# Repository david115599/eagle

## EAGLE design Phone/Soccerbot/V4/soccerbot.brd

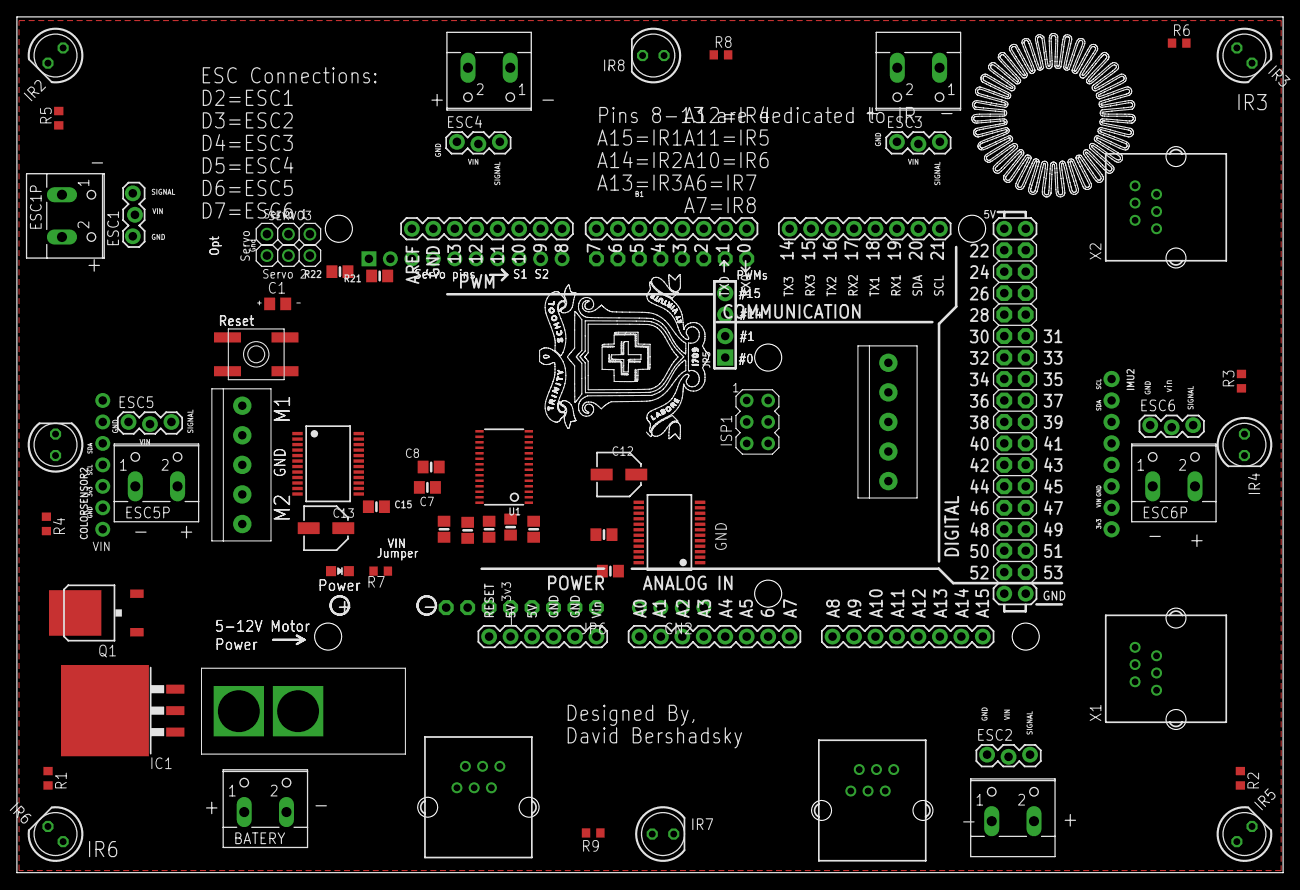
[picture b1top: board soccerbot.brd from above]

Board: 2 copper layers, 149.8 x 101.3 mm, 70 parts (0 on the bottom side), 67 nets, no tracks yet.

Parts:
B1: ARDUINO_MEGA_R3FULL; ARDUINO_MEGA
BATERY: W237-102
C1: C0805
C7, C8, C11: 0.1uF; 0805-NO
C12: 47uF/16v; PANASONIC_C
C13: 47uF+/16v; PANASONIC_C
C15, C16: 10uF; 0805-NO
CN2: 1X4-CLEANBIG; 1X04-CLEANBIG
COLORSENSOR2: 1X07_ROUND_70
D0-1: 1X08-CLEANBIG
ESC1, ESC2, ESC3, ESC4, ESC5, ESC6: 1X03_LOCK
ESC1P, ESC2P, ESC3P, ESC4P, ESC5P, ESC6P: W237-102
IC1: LM340S-05; TO263-3
IC2, IC4: SSOP24
IMU2: 1X08_ROUND_76
IR1, IR2, IR3, IR4, IR5, IR6, IR7, IR8: LED5MM
ISP1: AVRISP-6; AVRISP
J3, J4: 1X5; 1X05-3.5MM
JP5: 1X04_ROUND_76
JP6: 1X08-CLEANBIG
JP7: 1X10_ROUND70
LED2: Green; CHIPLED_0805_NOOUTLINE
Q1: AOD417; D-PAK_TO252AA
R1, R2, R3, R5, R6, R8, R9: 49.9k; R0603
R4: R0603
R7: 150ohm; R0603
R15, R16, R17, R19, R20: 0805-NO
R21, R22: 10K; 0805-NO
SERVO3, SERVO4: 1X03
SW2: SPST_TACT-EVQQ2; EVQ-Q2
U1: PCA9685; TSSOP28
U$2: TOGGLESWITCH
X1, X2, X3, X4: NXT-SOCKET

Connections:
3.3V: B1.3.3V, JP6.5, X1.4, X2.4, X3.4, X4.4
5.5V: B1.5V@0, B1.5V@1, B1.5V@2, C7.1, C8.1, C11.1, C15.1, C16.1, COLORSENSOR2.1, ESC1.2, ESC2.2, ESC3.2, ESC4.2, ESC5.2, ESC6.2, IC2.19, IC2.20, IC4.19, IC4.20, IMU2.7, IR1.K, IR2.K, IR3.K, IR4.K, IR5.K, IR6.K, IR7.K, IR8.K, ISP1.2, JP6.4, LED2.A, R21.2, R22.2, U1.24, U1.28
A0: R15.2, U1.1
A0A: B1.A0, CN2.4
A1: R16.2, U1.2
A1A: B1.A1, CN2.3
A2: R17.2, U1.3
A2A: B1.A2, CN2.2
A3: R19.2, U1.4
A3A: B1.A3, CN2.1
A4: R20.2, U1.5
A6: B1.A6, IR7.A, R9.1
A7: B1.A7, IR8.A, R8.1
A10: B1.A10, IR6.A, R1.1
A11: B1.A11, IR5.A, R2.1
A12: B1.A12, IR4.A, R3.1
A13: B1.A13, IR3.A, R6.1
A14: B1.A14, IR2.A, R5.1
A15: B1.A15, IR1.A, R4.1
AREF: B1.AREF, JP7.3
BAT+: B1.VIN, C12.+, C13.+, ESC1P.2, ESC2P.2, ESC3P.2, ESC4P.2, ESC5P.2, ESC6P.2, IC1.3, IC2.13, IC2.14, IC2.24, IC4.13, IC4.14, IC4.24, JP6.1, Q1.4, X1.1, X2.1, X3.1, X4.1
D0: B1.0, D0-1.1
D1: B1.1, D0-1.2
D2: B1.2, D0-1.3, ESC1.3
D3: B1.3, D0-1.4, ESC2.3
D4: B1.4, D0-1.5, ESC3.3
D5: B1.5, D0-1.6, ESC4.3
D6: B1.6, D0-1.7, ESC5.3
D7: B1.7, D0-1.8, ESC6.3
D8: B1.8, JP7.10
D9: B1.9, JP7.9, SERVO4.3
D10: B1.10, JP7.8, SERVO3.3
D11: B1.11, JP7.7
D12: B1.12, JP7.6
D13: B1.13, JP7.5
GND: B1.GND@0, B1.GND@1, B1.GND@2, B1.GND@3, B1.GND@4, BATERY.2, C1.2, C7.2, C8.2, C11.2, C12.-, C13.-, C15.2, C16.2, COLORSENSOR2.2, ESC1.1, ESC1P.1, ESC2.1, ESC2P.1, ESC3.1, ESC3P.1, ESC4.1, ESC4P.1, ESC5.1, ESC5P.1, ESC6.1, ESC6P.1, IC1.1, IC2.3, IC2.4, IC2.9, IC2.10, IC2.18, IC4.3, IC4.4, IC4.9, IC4.10, IC4.18, IMU2.6, ISP1.6, J3.3, J4.3, JP6.2, JP6.3, JP7.4, Q1.1, R1.2, R2.2, R3.2, R4.2, R5.2, R6.2, R7.1, R8.2, R9.2, R15.1, R16.1, R17.1, R19.1, R20.1, SERVO3.1, SERVO4.1, SW2.A, SW2.A', U1.14, U1.23, U1.25, X1.2, X1.3, X2.2, X2.3, X3.2, X3.3, X4.2, X4.3
M1A1: IC2.1, IC2.2, J3.5
M1B1: IC2.5, IC2.6, J3.4
M2A1: IC2.11, IC2.12, J3.1
M2B1: IC2.7, IC2.8, J3.2
M3A1: IC4.1, IC4.2, J4.1
M3B1: IC4.5, IC4.6, J4.2
M4A1: IC4.11, IC4.12, J4.5
M4B1: IC4.7, IC4.8, J4.4
unnamed: LED2.C, R7.2
unnamed: BATERY.1, U$2.IN
unnamed: Q1.3, U$2.OUT
PWM0: JP5.1, U1.6
PWM1: JP5.2, U1.7
PWM2: IC4.23, U1.8
PWM3: IC4.22, U1.9
PWM4: IC4.21, U1.10
PWM5: IC4.17, U1.11
PWM6: IC4.16, U1.12
PWM7: IC4.15, U1.13
PWM8: IC2.23, U1.15
PWM9: IC2.22, U1.16
PWM10: IC2.21, U1.17
PWM11: IC2.17, U1.18
PWM12: IC2.16, U1.19
PWM13: IC2.15, U1.20
PWM14: JP5.3, U1.21
PWM15: JP5.4, U1.22
RESET: B1.RESET, JP6.6, SW2.B, SW2.B'
SCL: B1.21, B1.A5, COLORSENSOR2.4, IMU2.1, JP7.1, R22.1, U1.26, X1.5, X2.5, X3.5, X4.5
SDA: B1.20, B1.A4, COLORSENSOR2.5, IMU2.2, JP7.2, R21.1, U1.27, X1.6, X2.6, X3.6, X4.6
SERVO5V: C1.1, IC1.TAB, SERVO3.2, SERVO4.2

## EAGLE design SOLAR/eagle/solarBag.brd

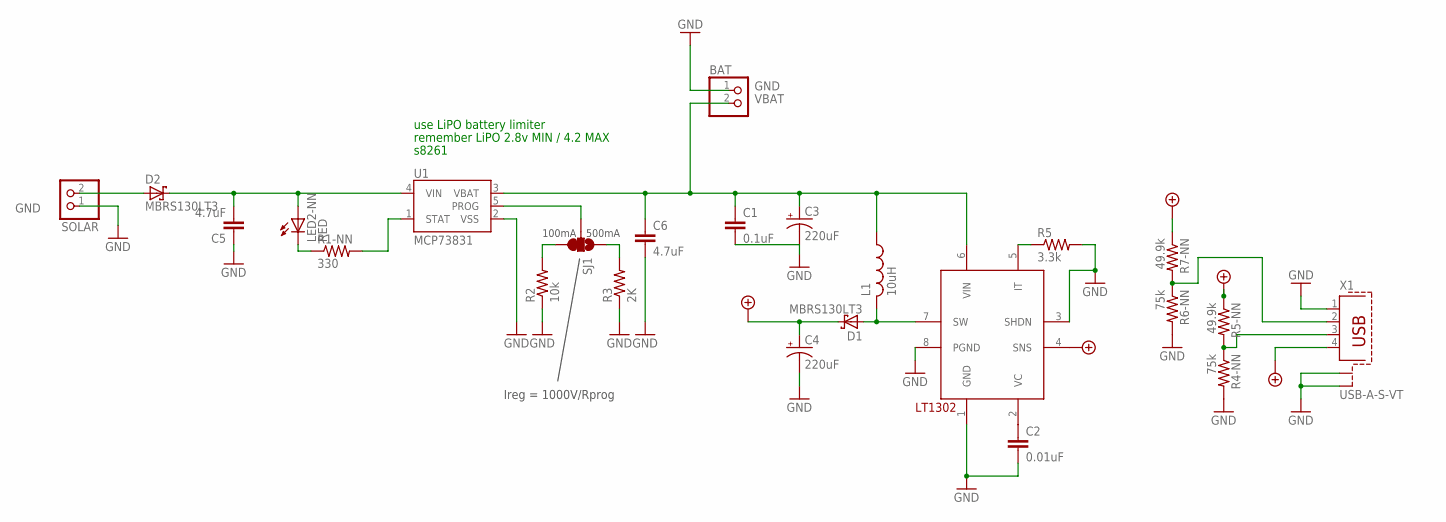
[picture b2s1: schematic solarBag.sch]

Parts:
BAT: PINHD-1X2; 1X02
C1: 0.1uF; C1206
C2: 0.01uF; C1206
C3, C4: 220uF; PANASONIC_F@1
C5, C6: 4.7uF; C1206
D1, D2: MBRS130LT3; SMB
L1: 10uH; SDR0403
LED2-NN: RED; LED-1206
R1-NN: 330; R1206
R2: 10k; R1206
R3: 2K; R1206
R4-NN, R6-NN: 75k; R0805
R5: 3.3k; R0805
R5-NN, R7-NN: 49.9k; R1206
SJ1: SOLDERJUMPER_2WAYS; SJ_3
SOLAR: PINHD-1X2; 1X02
U1: MCP73831; SOT23-5
U2: LT1302; SOIC8
X1: USB-A-S-VT

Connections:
+5V: C4.+, D1.C, R5-NN.1, R7-NN.1, U2.4 (SNS), X1.4
D+: R6-NN.1, R7-NN.2, X1.2
D-: R4-NN.1, R5-NN.2, X1.3
GND: BAT.1, C1.2, C2.2, C3.-, C4.-, C5.1, C6.2, R2.1, R3.1, R4-NN.2, R5.2, R6-NN.2, SOLAR.1, U1.2 (VSS), U2.1 (GND), U2.3 (SHDN), U2.8 (PGND), X1.1, X1.S1, X1.S2
unnamed: D1.A, L1.P$2 (2), U2.7 (SW)
unnamed: R1-NN.2, U1.1 (STAT)
unnamed: R2.2, SJ1.3
unnamed: R5.1, U2.5 (IT)
unnamed: LED2-NN.C, R1-NN.1
unnamed: R3.2, SJ1.1
unnamed: C2.1, U2.2 (VC)
unnamed: C5.2, D2.C, LED2-NN.A, U1.4 (VIN)
unnamed: D2.A, SOLAR.2
PROG: SJ1.2, U1.5 (PROG)
VBAT: BAT.2, C1.1, C3.+, C6.1, L1.P$1 (1), U1.3 (VBAT), U2.6 (VIN)

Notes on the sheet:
100mA
500mA
Ireg = 1000V/Rprog
remember LiPO 2.8v MIN / 4.2 MAX
s8261
use LiPO battery limiter

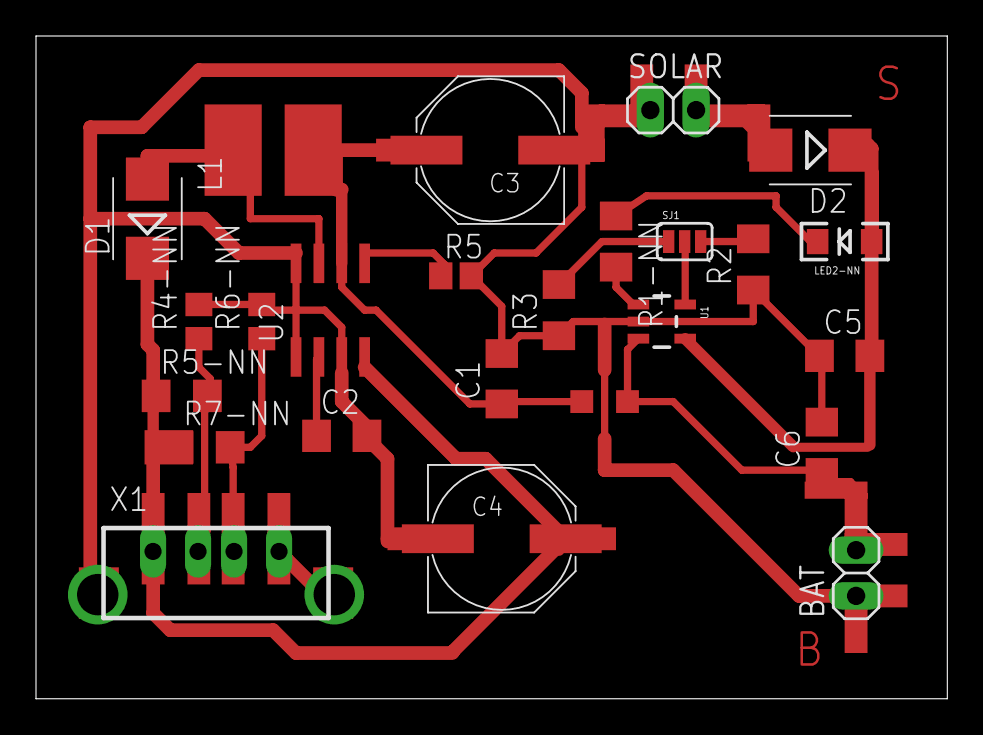
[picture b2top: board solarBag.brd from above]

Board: 2 copper layers, 50.6 x 36.8 mm, 24 parts (0 on the bottom side), 15 nets.

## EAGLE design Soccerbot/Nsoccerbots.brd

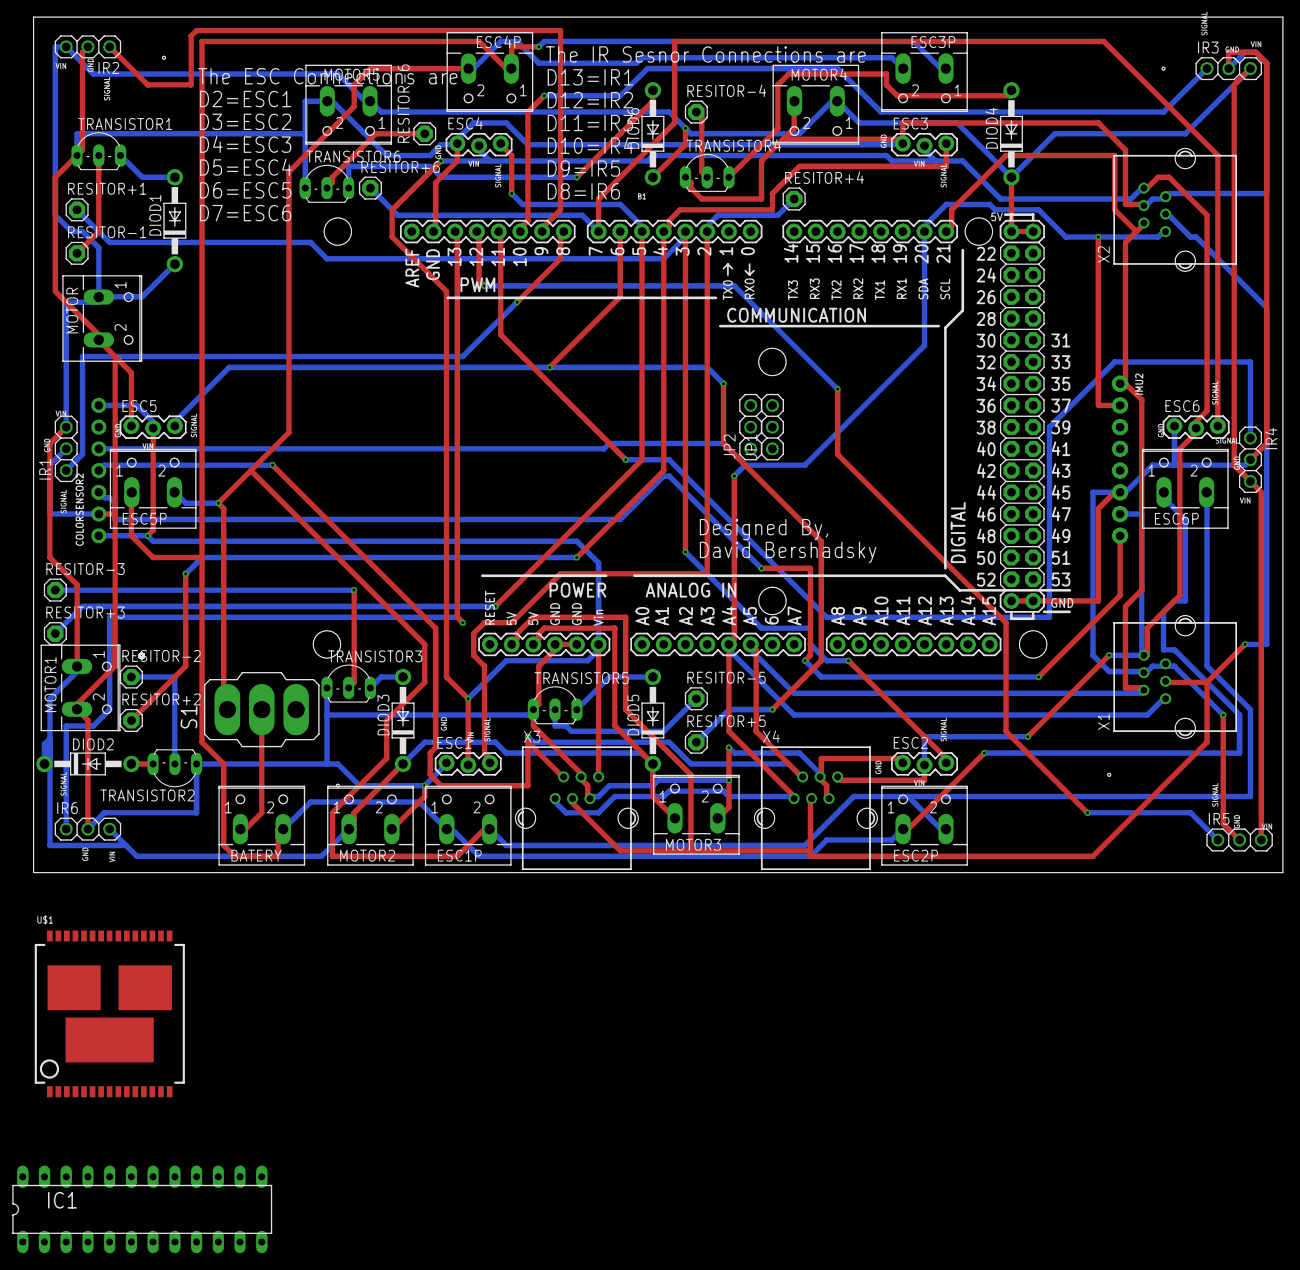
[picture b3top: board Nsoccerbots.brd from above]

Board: 2 copper layers, 146.0 x 100.0 mm, 61 parts (0 on the bottom side), 34 nets.

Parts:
B1: ARDUINO_MEGA_R3FULL; ARDUINO_MEGA
BATERY: W237-102
COLORSENSOR2: 1X07_ROUND_70
DIOD1, DIOD2, DIOD3, DIOD4, DIOD5, DIOD6: 1N4004; DO41-10
ESC1, ESC2, ESC3, ESC4, ESC5, ESC6: 1X03_LOCK
ESC1P, ESC2P, ESC3P, ESC4P, ESC5P, ESC6P: W237-102
IC1: 33035P; DIL24S
IMU2: 1X08_ROUND_76
IR1, IR2, IR3, IR4, IR5, IR6: 1X03
JP1, JP2: 1X03
MOTOR, MOTOR1, MOTOR2, MOTOR3, MOTOR4, MOTOR5: W237-102
RESITOR+1, RESITOR+2, RESITOR+3, RESITOR+4, RESITOR+5, RESITOR+6: 1X01
RESITOR-1, RESITOR-2, RESITOR-3, RESITOR-4, RESITOR-5, RESITOR-6: 1X01
S1: 320-916
TRANSISTOR1, TRANSISTOR2, TRANSISTOR3, TRANSISTOR4, TRANSISTOR5, TRANSISTOR6: 2N2907; TO92-EBC-OVAL
U$1: VNH2SP30
X1, X2, X3, X4: NXT-SOCKET

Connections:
3.3V: B1.3.3V, X1.4, X2.4, X3.4, X4.4
5.5V: B1.5V@0, B1.5V@1, B1.5V@2, DIOD1.C, DIOD2.C, DIOD3.C, DIOD4.C, DIOD5.C, DIOD6.C, IR1.3, IR2.3, IR3.3, IR4.3, IR5.3, IR6.3, MOTOR.1, MOTOR1.1, MOTOR2.1, MOTOR3.1, MOTOR4.1, MOTOR5.1
+3V3: COLORSENSOR2.3, IMU2.8
BAT+: ESC1P.2, ESC2P.2, ESC3P.2, ESC4P.2, ESC5P.2, ESC6P.2, S1.1
BAT-: BATERY.2, ESC1P.1, ESC2P.1, ESC3P.1, ESC4P.1, ESC5P.1, ESC6P.1
D2: B1.2, ESC1.3, RESITOR+4.1
D3: B1.3, ESC2.3, RESITOR+1.1
D4: B1.4, ESC3.3, RESITOR+2.1
D5: B1.5, ESC4.3, RESITOR+3.1
D6: B1.6, ESC5.3, RESITOR+5.1
D7: B1.7, ESC6.3, RESITOR+6.1
D8: B1.8, IR1.1
D9: B1.9, IR2.1
D10: B1.10, IR3.1
D11: B1.11, IR4.1
D12: B1.12, IR5.1
D13: B1.13, IR6.1
GND: B1.GND@0, B1.GND@1, B1.GND@2, B1.GND@3, B1.GND@4, COLORSENSOR2.2, ESC1.1, ESC2.1, ESC3.1, ESC4.1, ESC5.1, ESC6.1, IC1.16, IMU2.6, IR1.2, IR2.2, IR3.2, IR4.2, IR5.2, IR6.2, MOTOR.2, MOTOR1.2, MOTOR2.2, MOTOR3.2, MOTOR4.2, MOTOR5.2, TRANSISTOR1.E, TRANSISTOR2.E, TRANSISTOR3.E, TRANSISTOR4.E, TRANSISTOR5.E, TRANSISTOR6.E, X1.2, X1.3, X2.2, X2.3, X3.2, X3.3, X4.2, X4.3
unnamed: RESITOR-1.1, TRANSISTOR1.B
unnamed: DIOD1.A, TRANSISTOR1.C
unnamed: RESITOR-4.1, TRANSISTOR4.B
unnamed: BATERY.1, S1.2
unnamed: RESITOR-2.1, TRANSISTOR2.B
unnamed: DIOD2.A, TRANSISTOR2.C
unnamed: RESITOR-3.1, TRANSISTOR3.B
unnamed: DIOD3.A, TRANSISTOR3.C
unnamed: RESITOR-5.1, TRANSISTOR5.B
unnamed: DIOD5.A, TRANSISTOR5.C
unnamed: DIOD4.A, TRANSISTOR4.C
unnamed: RESITOR-6.1, TRANSISTOR6.B
unnamed: DIOD6.A, TRANSISTOR6.C
SCL: B1.21, B1.A5, COLORSENSOR2.4, IMU2.1, X1.5, X2.5, X3.5, X4.5
SDA: B1.20, B1.A4, COLORSENSOR2.5, IMU2.2, X1.6, X2.6, X3.6, X4.6
VIN: B1.VIN, COLORSENSOR2.1, COLORSENSOR2.7, ESC1.2, ESC2.2, ESC3.2, ESC4.2, ESC5.2, ESC6.2, IMU2.7, X1.1, X2.1, X3.1, X4.1

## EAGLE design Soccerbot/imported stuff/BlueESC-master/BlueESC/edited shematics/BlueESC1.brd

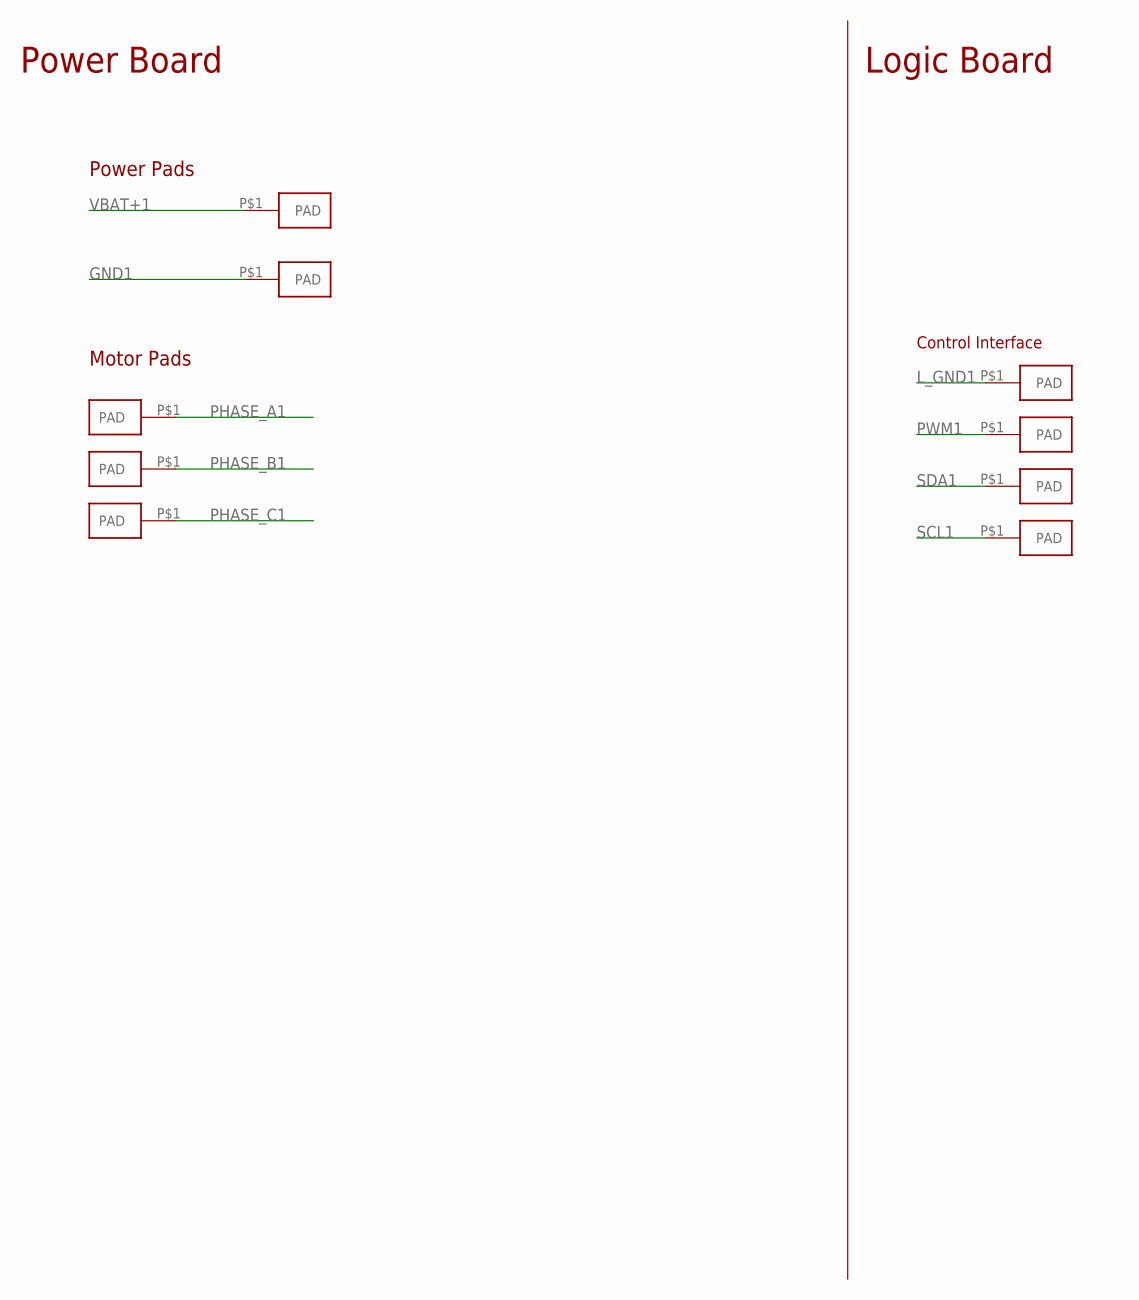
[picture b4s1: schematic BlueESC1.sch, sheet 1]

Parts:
U$1, U$2: PADPTH-MED; PAD-PTH-MED-1
U$5, U$6, U$7: PAD18AWG; PAD-PTH-18AWG-1
U$11, U$12, U$13, U$14: PAD1.5X3MM; PAD-1.5X3MM

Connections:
GND1: U$2.P$1; also elsewhere on the board
L_GND1: U$11.P$1; also elsewhere on the board
PHASE_A1: U$5.P$1; also elsewhere on the board
PHASE_B1: U$6.P$1; also elsewhere on the board
PHASE_C1: U$7.P$1; also elsewhere on the board
PWM1: U$14.P$1; also elsewhere on the board
SCL1: U$13.P$1; also elsewhere on the board
SDA1: U$12.P$1; also elsewhere on the board
VBAT+1: U$1.P$1; also elsewhere on the board

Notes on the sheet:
Power Pads
Motor Pads
Control Interface
Power Board
Logic Board

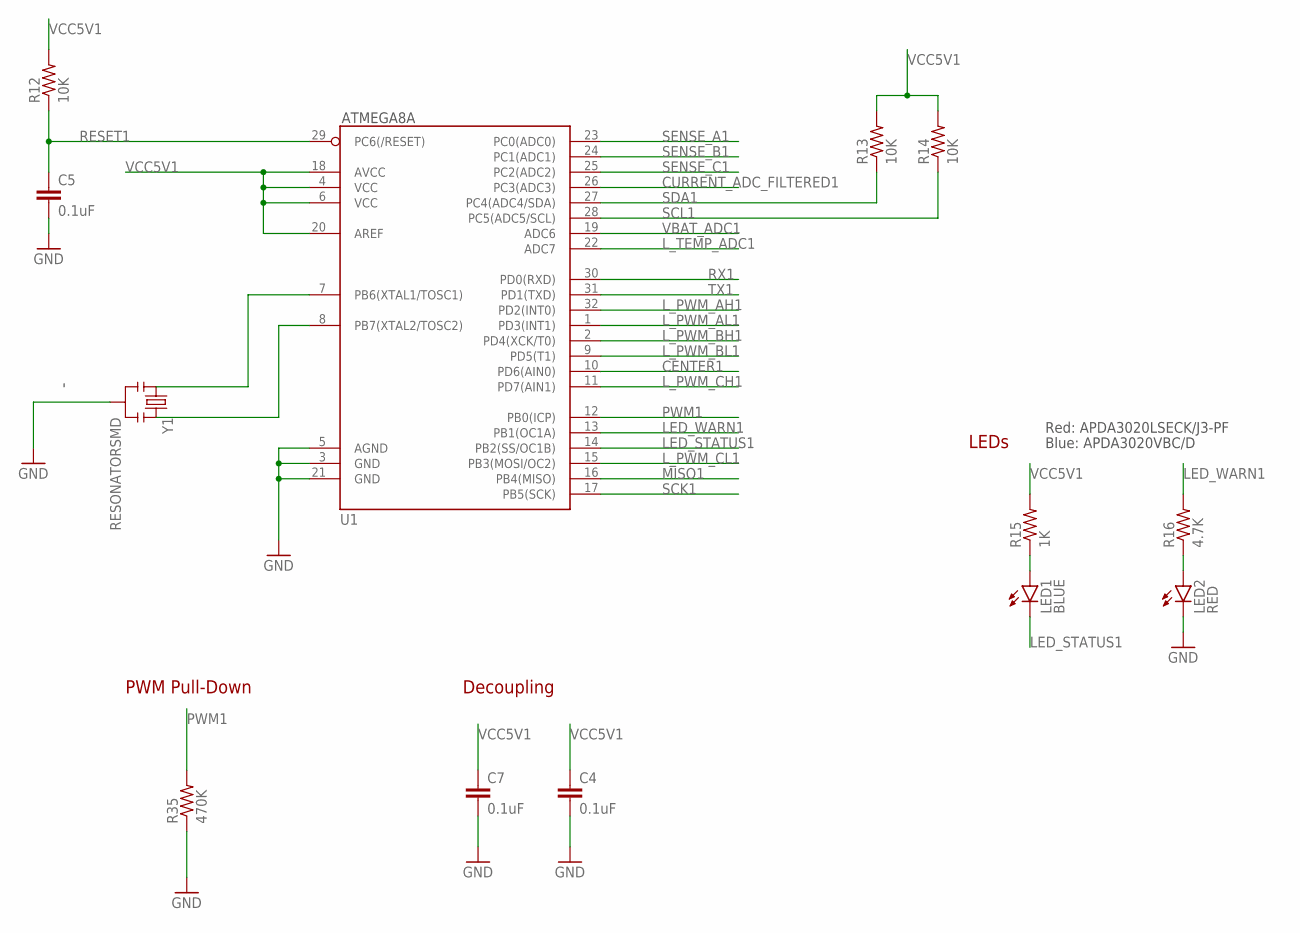
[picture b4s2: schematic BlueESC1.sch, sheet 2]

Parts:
C4, C5, C7: 0.1uF; 0603-CAP
LED1: BLUE; SMT-LED-3X2-RA
LED2: RED; SMT-LED-3X2-RA
R12, R13, R14: 10K; 0603-RES
R15: 1K; 0603-RES
R16: 4.7K; 0603-RES
R35: 470K; 0603-RES
U1: ATMEGA168; TQFP32-08
Y1: RESONATORSMD; RESONATOR-SMD

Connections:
CENTER1: U1.10 (PD6(AIN0)); also elsewhere on the board
CURRENT_ADC_FILTERED1: U1.26 (PC3(ADC3)); also elsewhere on the board
LED_STATUS1: LED1.2 (C), U1.14 (PB2(SS/OC1B))
LED_WARN1: R16.2, U1.13 (PB1(OC1A))
L_GND1: C4.2, C5.2, C7.2, LED2.2 (C), R35.1, U1.3 (GND), U1.5 (AGND), U1.21 (GND), Y1.2; also elsewhere on the board
L_PWM_AH1: U1.32 (PD2(INT0))
L_PWM_AL1: U1.1 (PD3(INT1))
L_PWM_BH1: U1.2 (PD4(XCK/T0))
L_PWM_BL1: U1.9 (PD5(T1))
L_PWM_CH1: U1.11 (PD7(AIN1))
L_PWM_CL1: U1.15 (PB3(MOSI/OC2))
L_TEMP_ADC1: U1.22 (ADC7)
MISO1: U1.16 (PB4(MISO))
unnamed: LED2.1 (A), R16.1
unnamed: U1.7 (PB6(XTAL1/TOSC1)), Y1.1
unnamed: U1.8 (PB7(XTAL2/TOSC2)), Y1.3
unnamed: LED1.1 (A), R15.1
PWM1: R35.2, U1.12 (PB0(ICP)); also elsewhere on the board
RESET1: C5.1, R12.1, U1.29 (PC6(/RESET))
RX1: U1.30 (PD0(RXD))
SCK1: U1.17 (PB5(SCK))
SCL1: R14.1, U1.28 (PC5(ADC5/SCL)); also elsewhere on the board
SDA1: R13.1, U1.27 (PC4(ADC4/SDA)); also elsewhere on the board
SENSE_A1: U1.23 (PC0(ADC0)); also elsewhere on the board
SENSE_B1: U1.24 (PC1(ADC1)); also elsewhere on the board
SENSE_C1: U1.25 (PC2(ADC2)); also elsewhere on the board
TX1: U1.31 (PD1(TXD))
VBAT_ADC1: U1.19 (ADC6); also elsewhere on the board
VCC5V1: C4.1, C7.1, R12.2, R13.2, R14.2, R15.2, U1.4 (VCC), U1.6 (VCC), U1.18 (AVCC), U1.20 (AREF); also elsewhere on the board

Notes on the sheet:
ATMEGA8A
Decoupling
LEDs
Red: APDA3020LSECK/J3-PF
Blue: APDA3020VBC/D
PWM Pull-Down

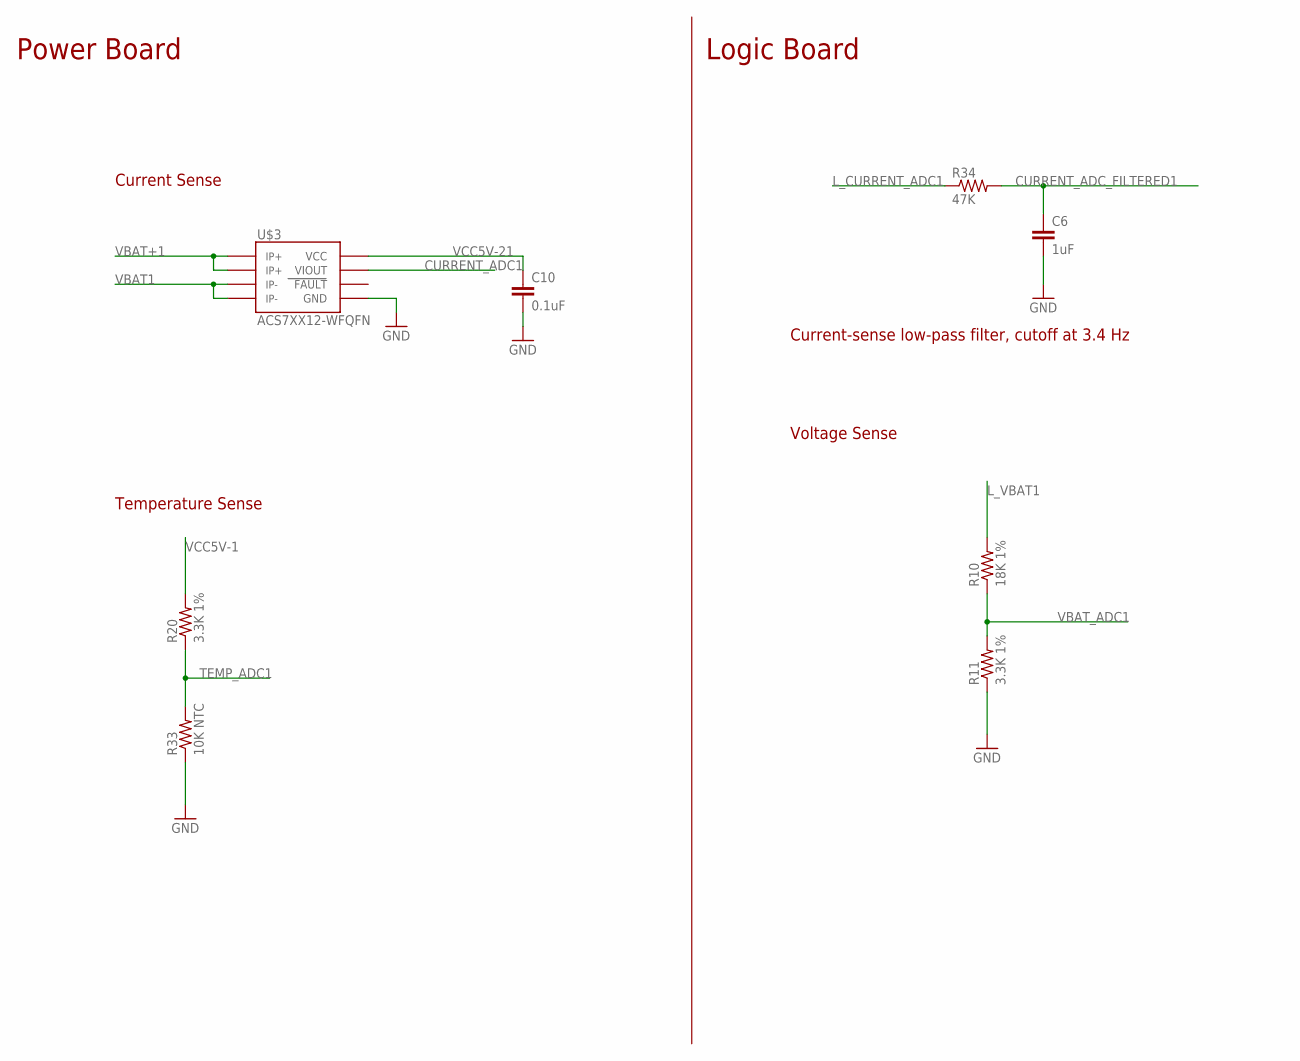
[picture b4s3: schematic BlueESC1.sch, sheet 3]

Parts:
C6: 1uF; 0603-CAP
C10: 0.1uF; 0603-CAP
R10: 18K 1%; 0603-RES
R11, R20: 3.3K 1%; 0603-RES
R33: 10K NTC; 0603-RES
R34: 47K; 0603-RES
U$3: ACS7XX12-WFQFN; 12-WFQFN

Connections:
CURRENT_ADC1: U$3.VIOUT
CURRENT_ADC_FILTERED1: C6.1, R34.2; also elsewhere on the board
GND1: C10.2, R33.1, U$3.GND; also elsewhere on the board
L_CURRENT_ADC1: R34.1
L_GND1: C6.2, R11.1; also elsewhere on the board
L_VBAT1: R10.2; also elsewhere on the board
TEMP_ADC1: R20.1, R33.2
VBAT1: U$3.IP-1, U$3.IP-2; also elsewhere on the board
VBAT+1: U$3.IP+1, U$3.IP+2; also elsewhere on the board
VBAT_ADC1: R10.1, R11.2; also elsewhere on the board
VCC5V-1: R20.2
VCC5V-21: C10.1, U$3.VCC

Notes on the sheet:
Power Board
Logic Board
Current-sense low-pass filter, cutoff at 3.4 Hz
Voltage Sense
Current Sense
Temperature Sense

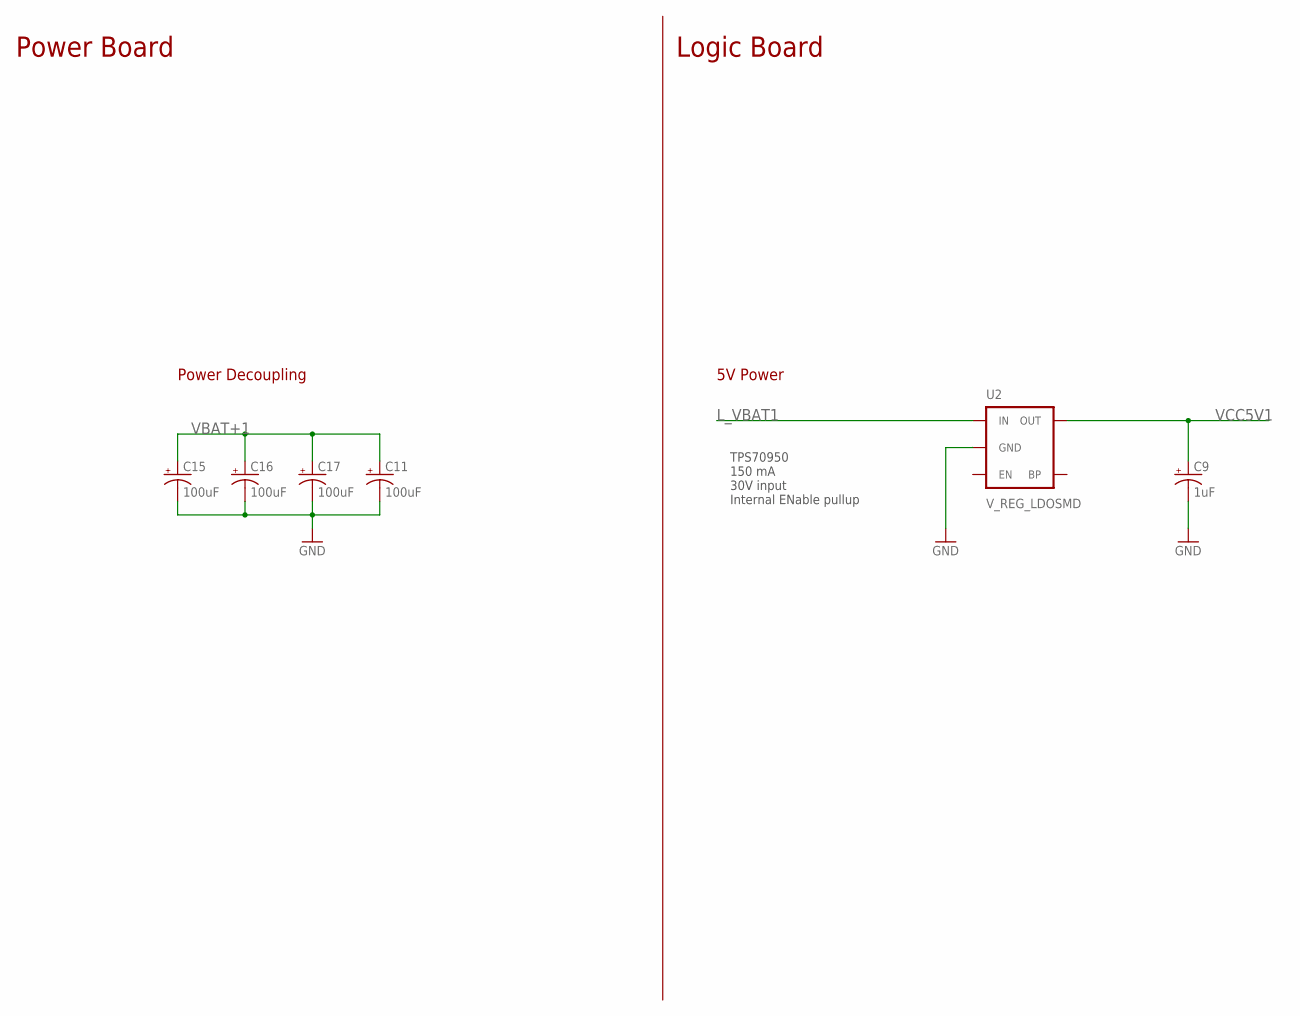
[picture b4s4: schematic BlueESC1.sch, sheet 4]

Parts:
C9: 1uF; EIA3216
C11, C15, C16, C17: 100uF; EIA7343
U2: V_REG_LDOSMD; SOT23-5

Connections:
GND1: C11.C (-), C15.C (-), C16.C (-), C17.C (-); also elsewhere on the board
L_GND1: C9.C (-), U2.2 (GND); also elsewhere on the board
L_VBAT1: U2.1 (IN); also elsewhere on the board
VBAT+1: C11.A (+), C15.A (+), C16.A (+), C17.A (+); also elsewhere on the board
VCC5V1: C9.A (+), U2.5 (OUT); also elsewhere on the board

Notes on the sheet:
Power Board
Logic Board
Power Decoupling
5V Power
TPS70950 150 mA 30V input Internal ENable pullup

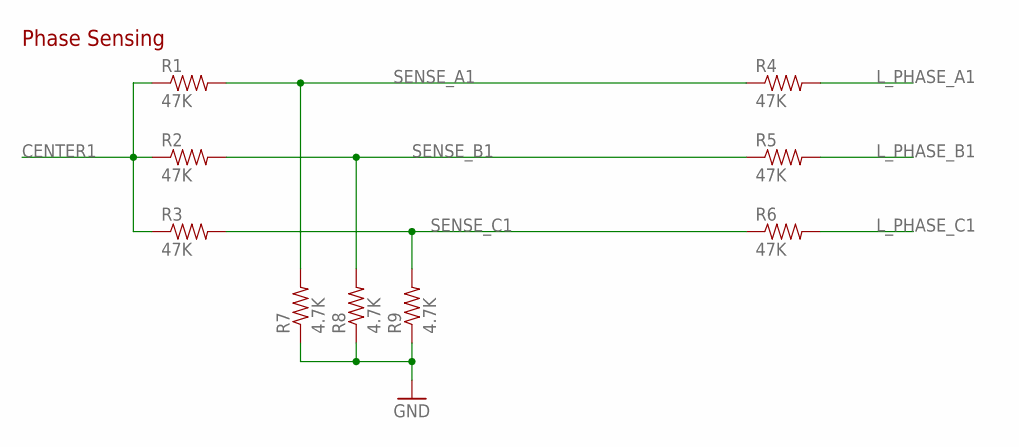
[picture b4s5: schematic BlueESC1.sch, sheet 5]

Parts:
R1, R2, R3, R4, R5, R6: 47K; 0603-RES
R7, R8, R9: 4.7K; 0603-RES

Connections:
CENTER1: R1.1, R2.1, R3.1; also elsewhere on the board
L_GND1: R7.1, R8.1, R9.1; also elsewhere on the board
L_PHASE_A1: R4.2
L_PHASE_B1: R5.2
L_PHASE_C1: R6.2
SENSE_A1: R1.2, R4.1, R7.2; also elsewhere on the board
SENSE_B1: R2.2, R5.1, R8.2; also elsewhere on the board
SENSE_C1: R3.2, R6.1, R9.2; also elsewhere on the board

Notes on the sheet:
Phase Sensing

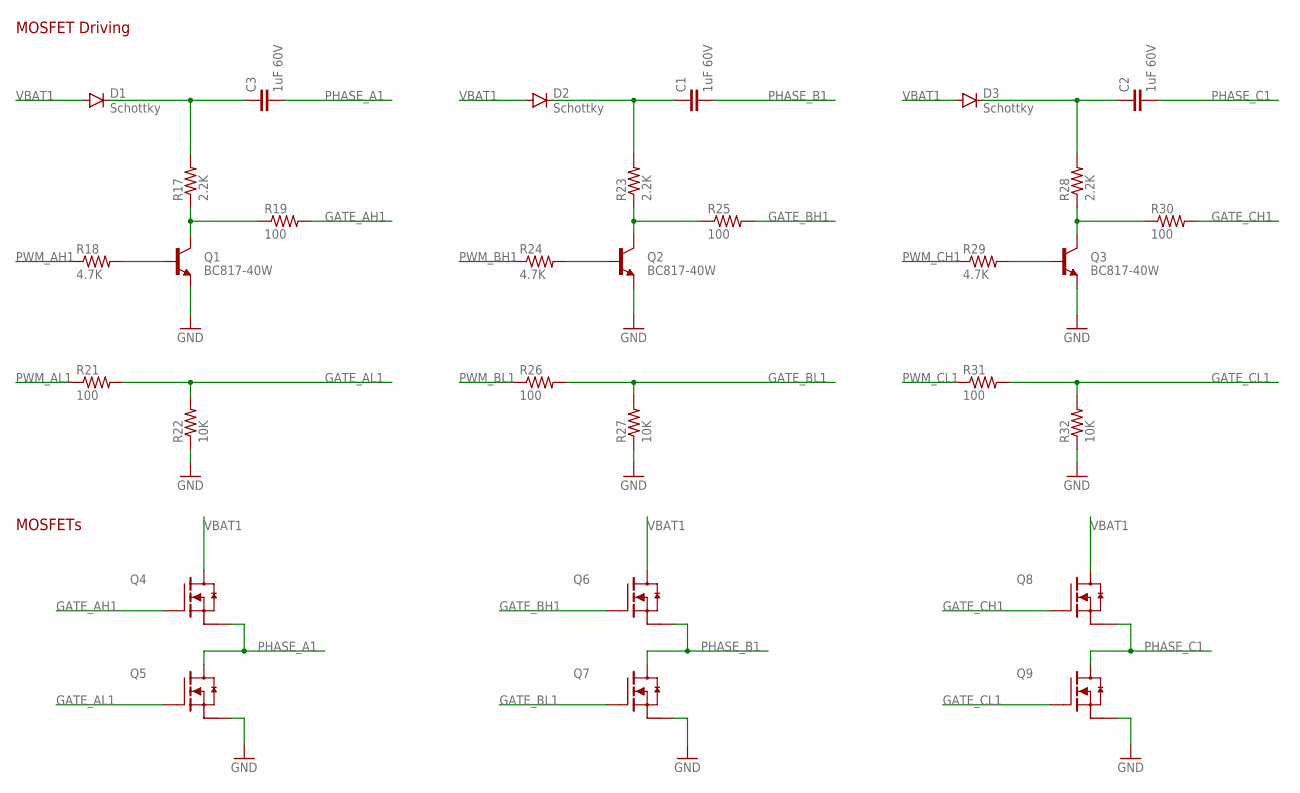
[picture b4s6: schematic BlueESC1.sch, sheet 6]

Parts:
C1, C2, C3: 1uF 60V; 0805
D1, D2, D3: Schottky; SOD-323
Q1, Q2, Q3: BC817-40W; SOT23
Q4, Q5, Q6, Q7, Q8, Q9: MOSFET-NCHANNEL; TDSON-8
R17, R23, R28: 2.2K; 0603-RES
R18, R24, R29: 4.7K; 0603-RES
R19, R21, R25, R26, R30, R31: 100; 0603-RES
R22, R27, R32: 10K; 0603-RES

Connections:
GATE_AH1: Q4.G, R19.2
GATE_AL1: Q5.G, R21.2, R22.2
GATE_BH1: Q6.G, R25.2
GATE_BL1: Q7.G, R26.2, R27.2
GATE_CH1: Q8.G, R30.2
GATE_CL1: Q9.G, R31.2, R32.2
GND1: Q1.2 (E), Q2.2 (E), Q3.2 (E), Q5.S1 (S), Q5.S2 (S), Q5.S3 (S), Q7.S1 (S), Q7.S2 (S), Q7.S3 (S), Q9.S1 (S), Q9.S2 (S), Q9.S3 (S), R22.1, R27.1, R32.1; also elsewhere on the board
unnamed: Q1.1 (B), R18.2
unnamed: Q1.3 (C), R17.1, R19.1
unnamed: Q2.1 (B), R24.2
unnamed: Q2.3 (C), R23.1, R25.1
unnamed: Q3.1 (B), R29.2
unnamed: Q3.3 (C), R28.1, R30.1
unnamed: C3.1, D1.C, R17.2
unnamed: C1.1, D2.C, R23.2
unnamed: C2.1, D3.C, R28.2
PHASE_A1: C3.2, Q4.S1 (S), Q4.S2 (S), Q4.S3 (S), Q5.D; also elsewhere on the board
PHASE_B1: C1.2, Q6.S1 (S), Q6.S2 (S), Q6.S3 (S), Q7.D; also elsewhere on the board
PHASE_C1: C2.2, Q8.S1 (S), Q8.S2 (S), Q8.S3 (S), Q9.D; also elsewhere on the board
PWM_AH1: R18.1
PWM_AL1: R21.1
PWM_BH1: R24.1
PWM_BL1: R26.1
PWM_CH1: R29.1
PWM_CL1: R31.1
VBAT1: D1.A, D2.A, D3.A, Q4.D, Q6.D, Q8.D; also elsewhere on the board

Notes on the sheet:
MOSFETs
MOSFET Driving

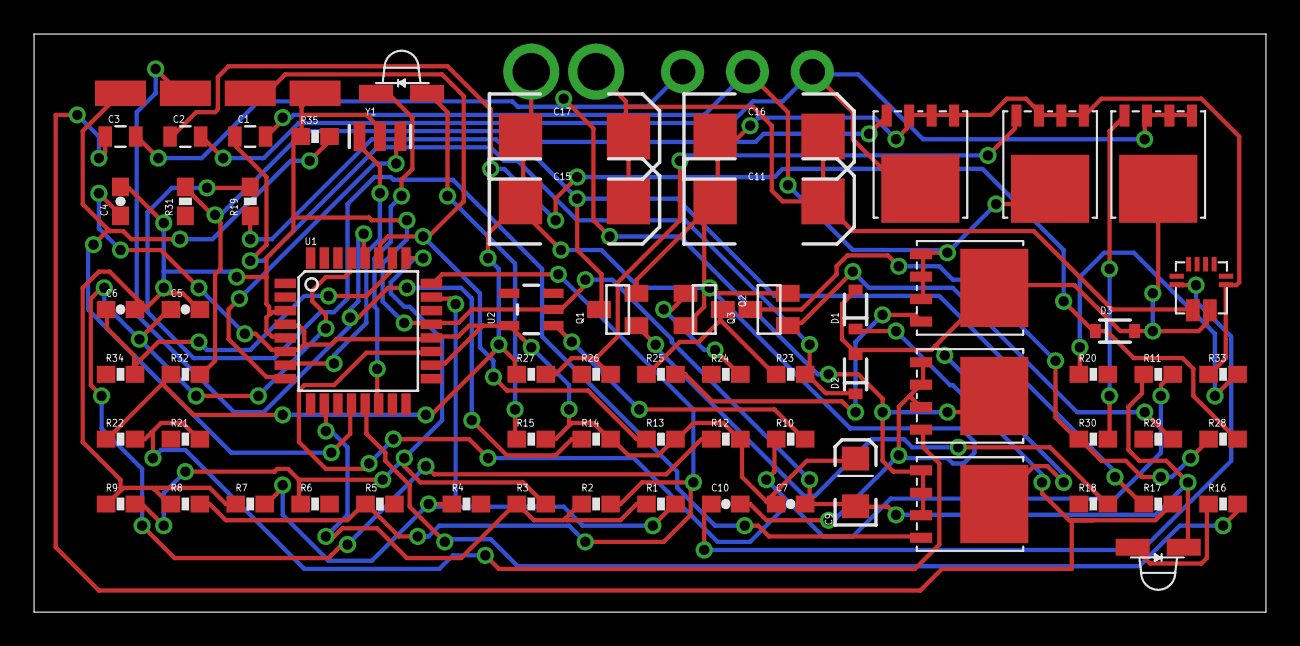
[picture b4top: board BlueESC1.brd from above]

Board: 2 copper layers, 72.4 x 34.0 mm, 75 parts (0 on the bottom side), 42 nets.

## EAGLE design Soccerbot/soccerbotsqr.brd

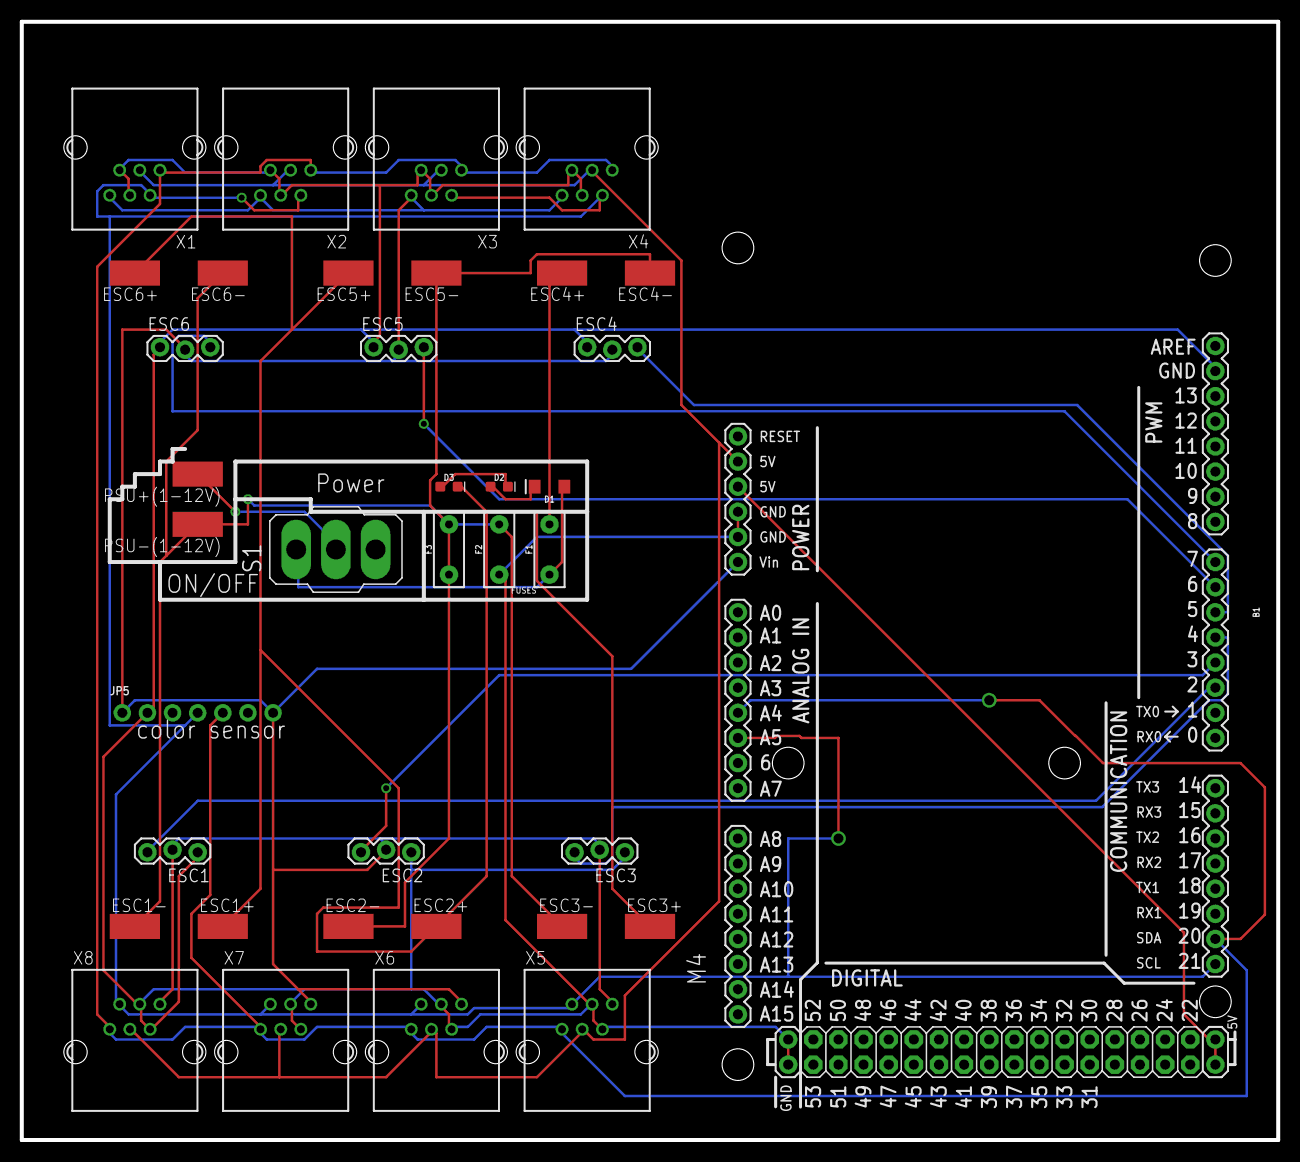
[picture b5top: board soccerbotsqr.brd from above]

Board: 2 copper layers, 127.0 x 113.0 mm, 37 parts (0 on the bottom side), 18 nets.

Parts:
B1: ARDUINO_MEGA_R3FULL; ARDUINO_MEGA
D1: BLUE; LED-1206
D2: GREEN; LED-0603
D3: RED; LED-0603
ESC1, ESC2, ESC3, ESC4, ESC5, ESC6: 1X03_LOCK
ESC1+, ESC1-, ESC2+, ESC2-, ESC3+, ESC3-, ESC4+, ESC4-, ESC5+, ESC5-, ESC6+, ESC6-: SMD2,54-5,08
F1, F2, F3: 72V/0.25A; PTH
JP5: 1X07_ROUND_70
PSU+(1-12V): SMD2,54-5,08
PSU-(1-12V): SMD2,54-5,08
S1: 320-916
X1, X2, X3, X4, X5, X6, X7, X8: NXT-SOCKET

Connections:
3.3V: B1.3.3V, X1.4, X2.4, X3.4, X4.4, X5.4, X6.4, X7.4, X8.4
5.5V: B1.5V@0, B1.5V@1, B1.5V@2
BAT+: D3.C, ESC1+.1, ESC2+.1, ESC3+.1, ESC4+.1, ESC5+.1, ESC6+.1, F1.P$2
BAT-: ESC1-.1, ESC2-.1, ESC3-.1, ESC4-.1, ESC5-.1, ESC6-.1, F2.P$2, F3.P$1, F3.P$2, PSU-(1-12V).1
D2: B1.2, ESC1.3
D3: B1.3, ESC2.3
D4: B1.4, ESC3.3
D5: B1.5, ESC4.3
D6: B1.6, ESC5.3
D7: B1.7, ESC6.3
GND: B1.GND@0, B1.GND@1, B1.GND@2, B1.GND@3, B1.GND@4, ESC1.1, ESC2.1, ESC3.1, ESC4.1, ESC5.1, ESC6.1, F2.P$1, JP5.2, X1.2, X1.3, X2.2, X2.3, X3.2, X3.3, X4.2, X4.3, X5.2, X5.3, X6.2, X6.3, X7.2, X7.3, X8.2, X8.3
unnamed: D1.C, D2.A
unnamed: PSU+(1-12V).1, S1.2
unnamed: D2.C, D3.A
unnamed: D1.A, F1.P$1, S1.1
SCL: B1.21, B1.A5, JP5.4, X1.5, X2.5, X3.5, X4.5, X5.5, X6.5, X7.5, X8.5
SDA: B1.20, B1.A4, JP5.5, X1.6, X2.6, X3.6, X4.6, X5.6, X6.6, X7.6, X8.6
VIN: B1.VIN, ESC1.2, ESC2.2, ESC3.2, ESC4.2, ESC5.2, ESC6.2, JP5.1, JP5.7, X1.1, X2.1, X3.1, X4.1, X5.1, X6.1, X7.1, X8.1

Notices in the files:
parts and their libraries:
SparkFun-Boards: Licensing: Creative Commons ShareAlike 4.0 International - https://creativecommons.org/licenses/by-sa/4.0
microbuilder: This work is placed in the public domain, and may be freely used for commercial and non-commercial work with the following conditions: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
